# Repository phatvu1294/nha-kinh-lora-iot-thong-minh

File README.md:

# Nhà kính LoRa IOT thông minh 
*Nhà kính LoRa IOT thông minh được phát triển dựa trên ESP8266, Arduino, LoRa*  

### Giới thiệu
Hệ thống bao gồm 2 Node có nhiệm vụ thu thập dữ liệu sau đó gửi về Gateway thông qua công nghệ LoRa. Dữ liệu này sẽ được Gateway xử lý và đẩy lên Website thông qua giao thức MQTT. Giao diện Website được thiết kế với Blogger cho phép giám sát các thông số ở bất kỳ nơi đâu mà chúng ta có internet.

### Tính năng
- Với IOT chúng ta có thể theo dõi thiết bị ở mọi nơi miễn là có internet
- Với LoRa chúng ta có khoảng cách truyền lên đến hàng kilomet
- Giao diện Website trực quan, dễ nhìn, tên miền blogspot miễn phí
- Phím nhấn cho phép cài đặt WiFi của Gateway 1 cách dễ dàng
- Mạch một lớp giúp dễ dàng làm thủ công, thích hợp với sinh viên nghiên cứu khoa học

### Thông số kỹ thuật
#### Node
- Điện áp vào: 9-12VDC
- Màn hình hiển thị: LCD1602
- Socket cảm biến: DHT11/DHT22/LM35/CB Đất

#### Gateway
- Điện áp vào: 9-12VDC
- Socket hiển thị: LCD I2C

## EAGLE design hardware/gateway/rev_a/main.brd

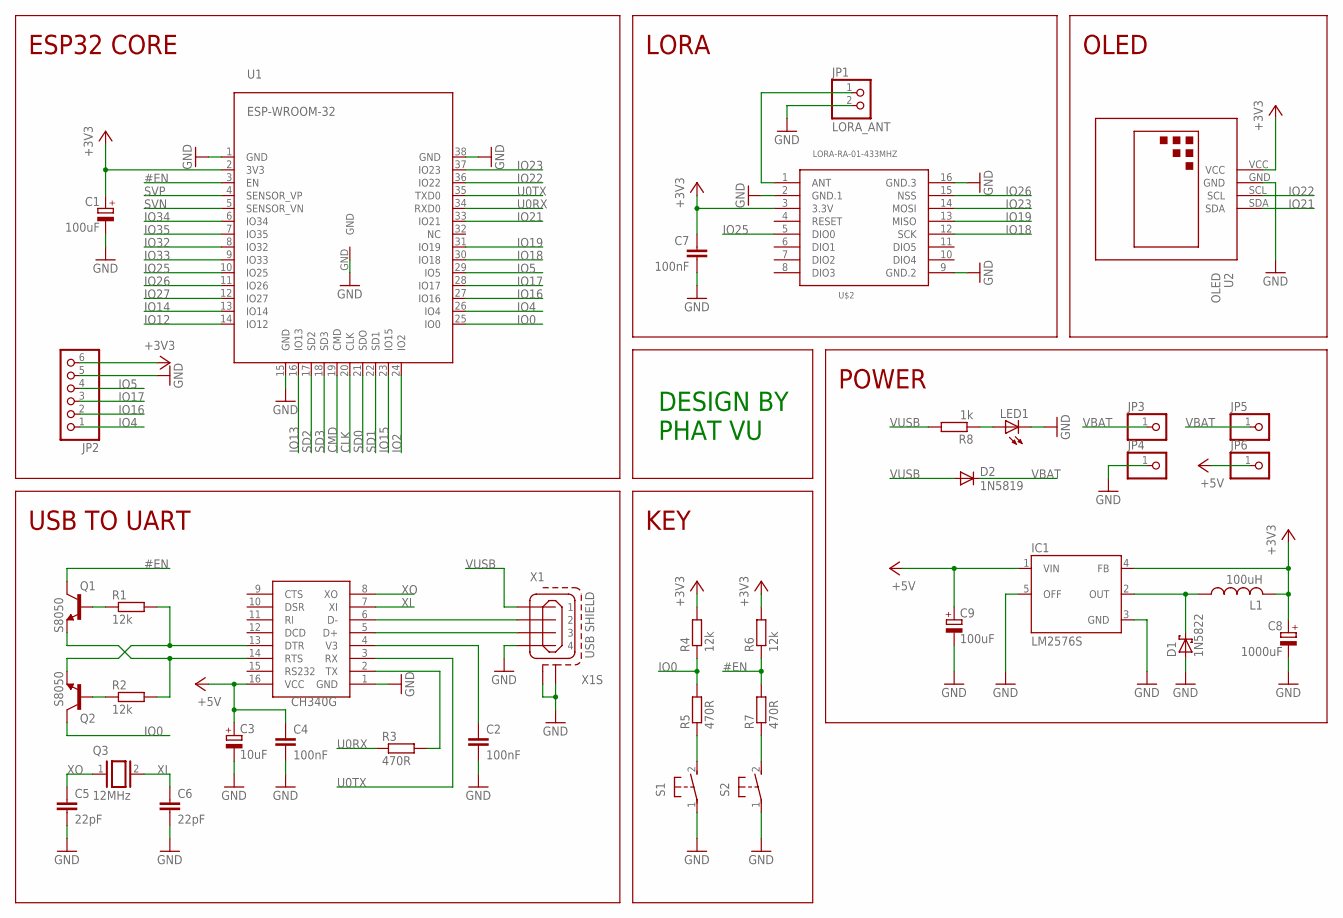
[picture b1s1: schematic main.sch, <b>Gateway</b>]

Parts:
C1, C9: 100uF; E5-10,5
C2, C4, C7: 100nF; C050-024X044
C3: 10uF; E2,5-6
C5, C6: 22pF; C050-024X044
C8: 1000uF; E5-13
D1: 1N5822; DO201T15
D2: 1N5819; DO41-10
IC1: LM2576S; TO263-5
JP1: LORA_ANT; 1X02
JP2: PINHD-1X6; 1X06
JP3, JP4, JP5, JP6: PINHD-1X1; 1X01
L1: 100uH; 6000-XXXX-RC
LED1: LED3MM
Q1, Q2: S8050; TO92-EBC
Q3: 12MHz; QS
R1, R2, R4, R6: 12k; 0207/10
R3, R5, R7: 470R; 0207/10
R8: 1k; 0207/10
S1, S2: 31-XX; B3F-31XX
U1: ESP-WROOM-32
U2: OLED; OLED-096-I2C
U$1: CH340G; SOIC16
U$2: LORA-RA-01-433MHZ; LORA-RA1-SMD
X1: USB SHIELD; 85-32004-00X

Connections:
#EN: Q1.C, R6.1, R7.2, U1.3 (EN)
+3V3: C1.+, C7.1, C8.+, IC1.4 (FB), JP2.6, L1.2, R4.2, R6.2, U1.2 (3V3), U2.VCC, U$2.3 (3.3V)
+5V: C3.+, C4.1, C9.+, IC1.1 (VIN), JP6.1, U$1.16 (VCC)
CLK: U1.20 (CLK)
CMD: U1.19 (CMD)
GND: C1.-, C2.2, C3.-, C4.2, C5.2, C6.2, C7.2, C8.-, C9.-, D1.A, IC1.3 (GND), IC1.5 (OFF), JP1.2, JP2.5, JP4.1, LED1.K (C), S1.1, S2.1, U1.1 (GND), U1.15 (GND), U1.38 (GND), U1.GND, U2.GND, U$1.1 (GND), U$2.2 (GND.1), U$2.9 (GND.2), U$2.16 (GND.3), X1.4, X1.M1 (S1), X1.M2 (S2)
IO0: Q2.C, R4.1, R5.2, U1.25 (IO0)
IO2: U1.24 (IO2)
IO4: JP2.1, U1.26 (IO4)
IO5: JP2.4, U1.29 (IO5)
IO12: U1.14 (IO12)
IO13: U1.16 (IO13)
IO14: U1.13 (IO14)
IO15: U1.23 (IO15)
IO16: JP2.2, U1.27 (IO16)
IO17: JP2.3, U1.28 (IO17)
IO18: U1.30 (IO18), U$2.12 (SCK)
IO19: U1.31 (IO19), U$2.13 (MISO)
IO21: U1.33 (IO21), U2.SDA
IO22: U1.36 (IO22), U2.SCL
IO23: U1.37 (IO23), U$2.14 (MOSI)
IO25: U1.10 (IO25), U$2.5 (DIO0)
IO26: U1.11 (IO26), U$2.15 (NSS)
IO27: U1.12 (IO27)
IO32: U1.8 (IO32)
IO33: U1.9 (IO33)
IO34: U1.6 (IO34)
IO35: U1.7 (IO35)
unnamed: JP1.1, U$2.1 (ANT)
unnamed: R3.2, U$1.2 (TX)
unnamed: U$1.6 (D-), X1.2
unnamed: U$1.5 (D+), X1.3
unnamed: C2.1, U$1.4 (V3)
unnamed: Q1.E, R2.2, U$1.14 (RTS)
unnamed: Q2.E, R1.2, U$1.13 (DTR)
unnamed: LED1.A, R8.1
unnamed: Q2.B, R2.1
unnamed: Q1.B, R1.1
unnamed: R7.1, S2.2 (S)
unnamed: R5.1, S1.2 (S)
unnamed: D1.C, IC1.2 (OUT), L1.1
SD0: U1.21 (SDO)
SD1: U1.22 (SD1)
SD2: U1.17 (SD2)
SD3: U1.18 (SD3)
SVN: U1.5 (SENSOR_VN)
SVP: U1.4 (SENSOR_VP)
U0RX: R3.1, U1.34 (RXD0)
U0TX: U1.35 (TXD0), U$1.3 (RX)
VBAT: D2.C, JP3.1, JP5.1
VUSB: D2.A, R8.2, X1.1
XI: C6.1, Q3.2, U$1.7 (XI)
XO: C5.1, Q3.1, U$1.8 (XO)

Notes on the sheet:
ESP32 CORE
USB TO UART
KEY
LORA
OLED
POWER
DESIGN BY PHAT VU

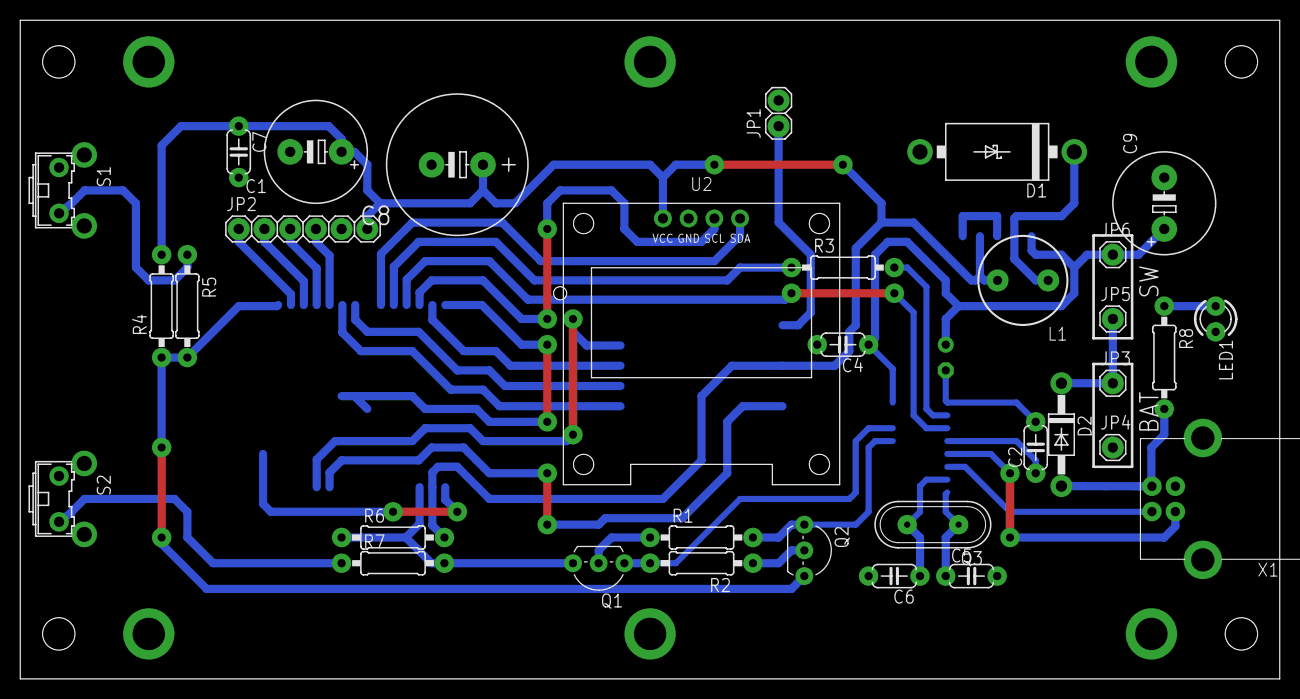
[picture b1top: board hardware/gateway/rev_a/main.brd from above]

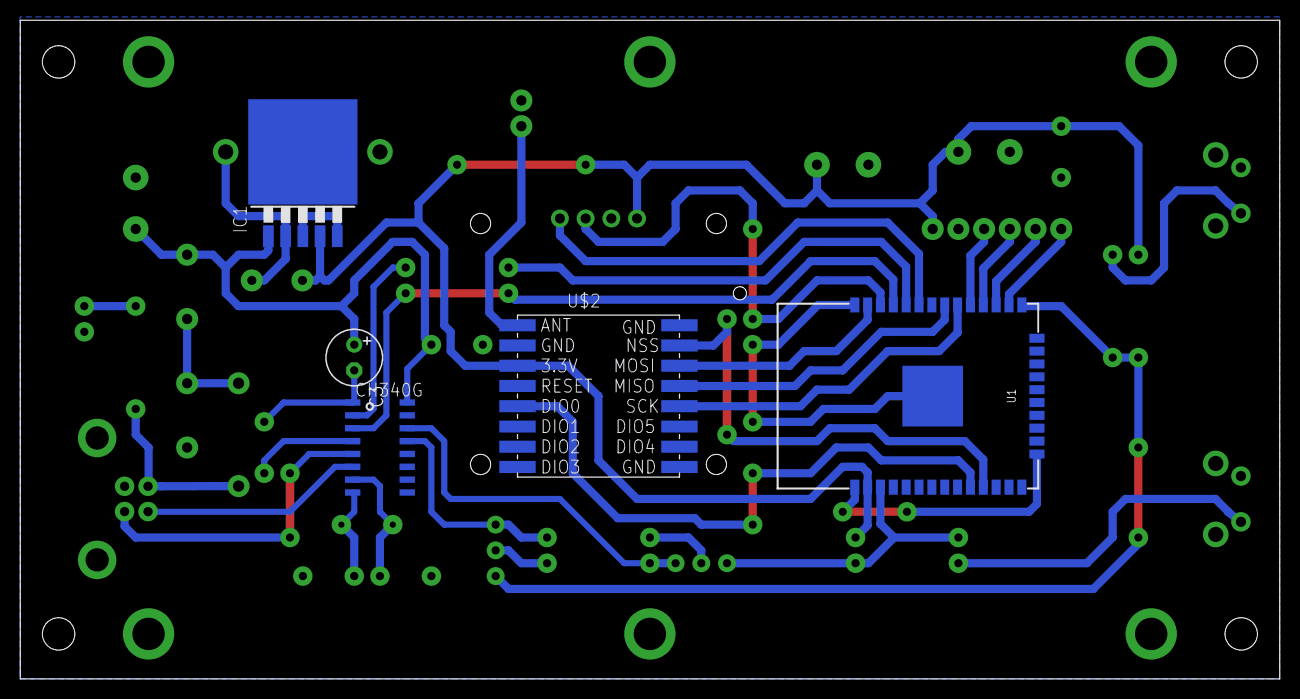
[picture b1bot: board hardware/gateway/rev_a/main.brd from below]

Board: 2 copper layers, 124.4 x 65.1 mm, 38 parts (5 on the bottom side), 35 nets.

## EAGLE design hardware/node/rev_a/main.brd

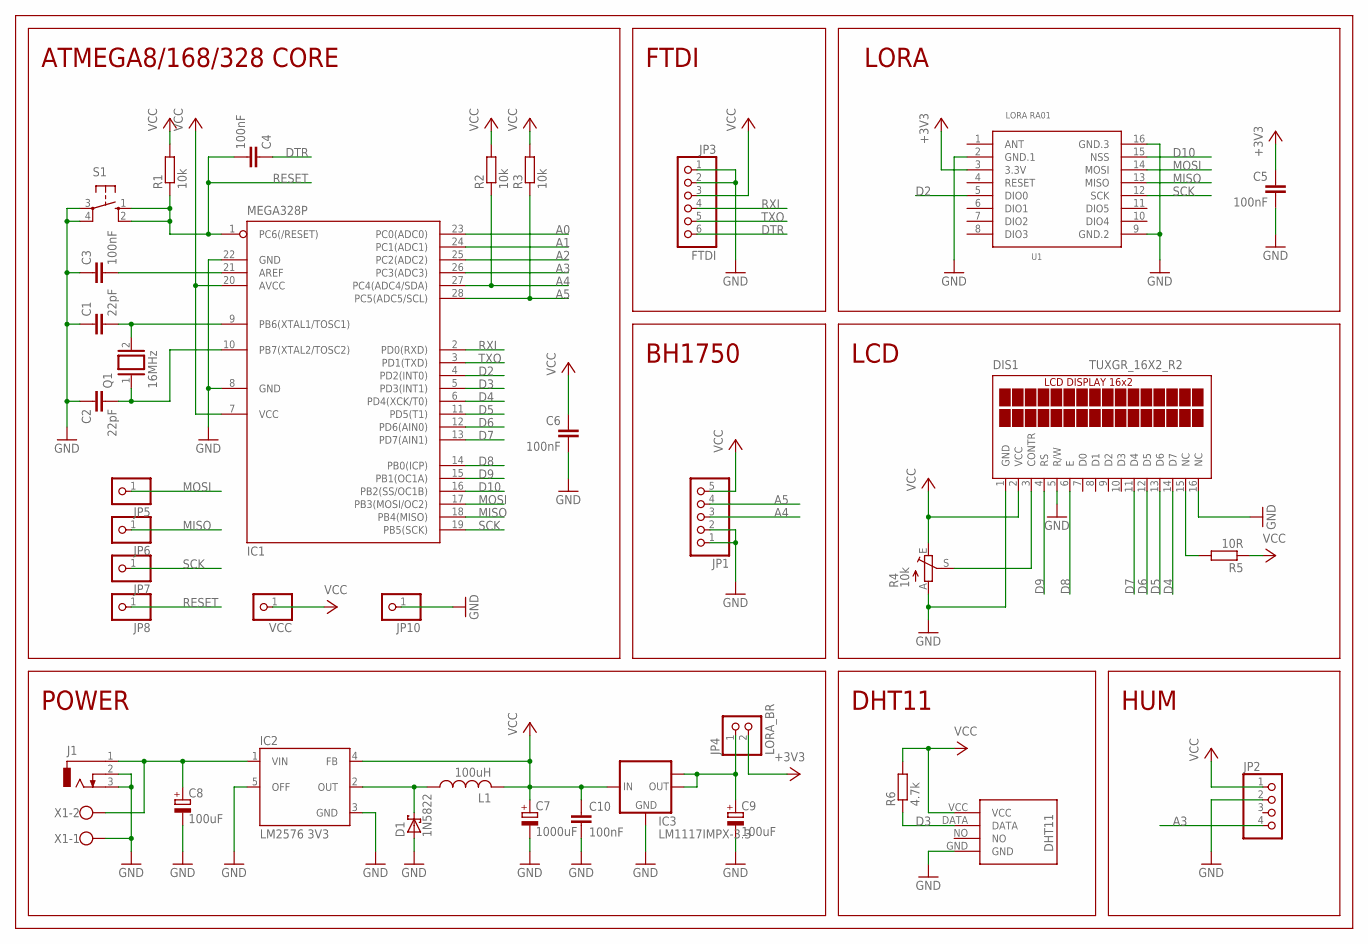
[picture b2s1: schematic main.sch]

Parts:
C1, C2: 22pF; C050-024X044
C3, C4, C5, C6, C10: 100nF; C050-024X044
C7: 1000uF; E5-13
C8: 100uF; E5-8,5
C9: 100uF; E3,5-10
D1: 1N5822; DO201T15
DIS1: TUXGR_16X2_R2
IC1: MEGA328P; DIL28-3
IC2: LM2576 3V3; TO263-5
IC3: LM1117IMPX-3.3; SOT223
J1: DCJ0303
JP1: PINHD-1X5; 1X05
JP2: PINHD-1X4; 1X04
JP3: FTDI; 1X06
JP4: LORA_BR; 1X02
JP5, JP6, JP7, JP8, JP10: PINHD-1X1; 1X01
L1: 100uH; 6000-XXXX-RC
Q1: 16MHz; QS
R1, R2, R3: 10k; 0207/10
R4: 10k; CA6V
R5: 10R; 0207/10
R6: 4.7k; 0207/10
S1: 10-XX; B3F-10XX
U1: LORA RA01; LORA-RA1-SMD
U$1: DHT11-PION.
VCC: PINHD-1X1; 1X01
X1: W237-102

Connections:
+3V3: C5.1, JP4.2, U1.3 (3.3V)
A0: IC1.23 (PC0(ADC0))
A1: IC1.24 (PC1(ADC1))
A2: IC1.25 (PC2(ADC2))
A3: IC1.26 (PC3(ADC3)), JP2.4
A4: IC1.27 (PC4(ADC4/SDA)), JP1.3, R2.1
A5: IC1.28 (PC5(ADC5/SCL)), JP1.4, R3.1
D2: IC1.4 (PD2(INT0)), U1.5 (DIO0)
D3: IC1.5 (PD3(INT1)), R6.1, U$1.DATA
D4: DIS1.14 (D7), IC1.6 (PD4(XCK/T0))
D5: DIS1.13 (D6), IC1.11 (PD5(T1))
D6: DIS1.12 (D5), IC1.12 (PD6(AIN0))
D7: DIS1.11 (D4), IC1.13 (PD7(AIN1))
D8: DIS1.6 (E), IC1.14 (PB0(ICP))
D9: DIS1.4 (RS), IC1.15 (PB1(OC1A))
D10: IC1.16 (PB2(SS/OC1B)), U1.15 (NSS)
DTR: C4.1, JP3.6
GND: C1.1, C2.1, C3.1, C5.2, C6.2, C7.-, C8.-, C9.-, C10.2, D1.A, DIS1.1 (GND), DIS1.5 (R/W), DIS1.16 (NC), IC1.8 (GND), IC1.22 (GND), IC2.3 (GND), IC2.5 (OFF), IC3.1 (GND), J1.2, J1.3, JP1.1, JP1.2, JP2.2, JP3.1, JP3.2, JP10.1, R4.A, S1.3, S1.4 (P1), U1.2 (GND.1), U1.9 (GND.2), U1.16 (GND.3), U$1.GND, X1.1
MISO: IC1.18 (PB4(MISO)), JP6.1, U1.13 (MISO)
MOSI: IC1.17 (PB3(MOSI/OC2)), JP5.1, U1.14 (MOSI)
unnamed: C1.2, IC1.9 (PB6(XTAL1/TOSC1)), Q1.2
unnamed: C2.2, IC1.10 (PB7(XTAL2/TOSC2)), Q1.1
unnamed: C3.2, IC1.21 (AREF)
unnamed: C8.+, IC2.1 (VIN), J1.1, X1.2
unnamed: D1.C, IC2.2 (OUT), L1.1
unnamed: C9.+, IC3.2 (OUT), IC3.TAB (OUT1), JP4.1
unnamed: DIS1.15 (NC), R5.2
unnamed: DIS1.3 (CONTR), R4.S
RESET: C4.2, IC1.1 (PC6(/RESET)), JP8.1, R1.1, S1.1 (S), S1.2 (S1)
RXI: IC1.2 (PD0(RXD)), JP3.4
SCK: IC1.19 (PB5(SCK)), JP7.1, U1.12 (SCK)
TXO: IC1.3 (PD1(TXD)), JP3.5
VCC: C6.1, C7.+, C10.1, DIS1.2 (VCC), IC1.7 (VCC), IC1.20 (AVCC), IC2.4 (FB), IC3.3 (IN), JP1.5, JP2.1, JP3.3, L1.2, R1.2, R2.2, R3.2, R4.E, R5.1, R6.2, U$1.VCC, VCC.1

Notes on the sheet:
LORA
ATMEGA8/168/328 CORE
FTDI
POWER
BH1750
LCD
DHT11
HUM

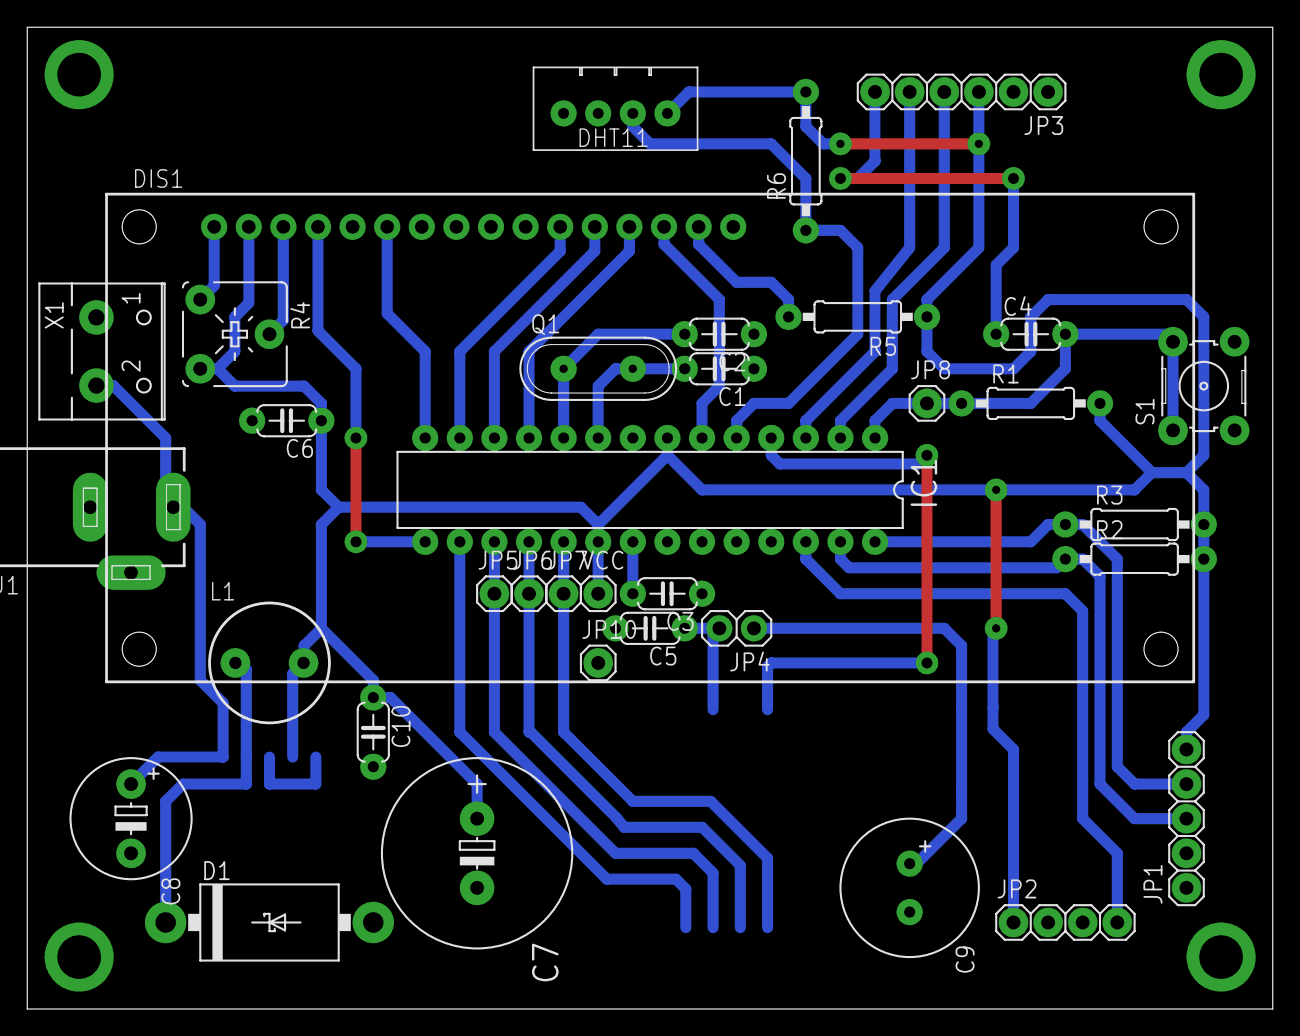
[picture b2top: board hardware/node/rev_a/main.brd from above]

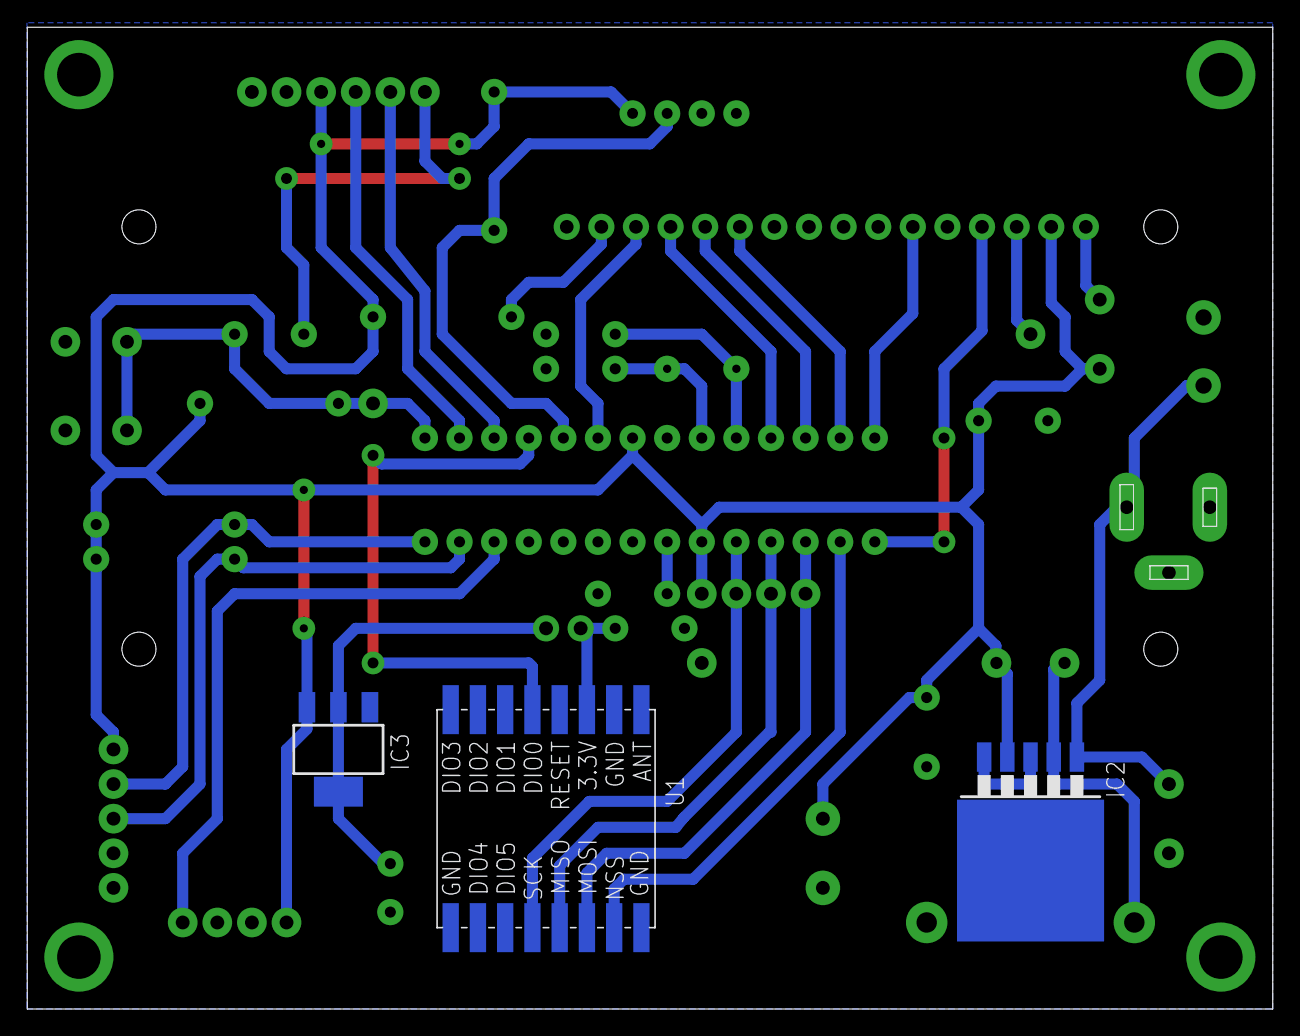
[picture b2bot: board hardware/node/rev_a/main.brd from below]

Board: 2 copper layers, 91.4 x 72.1 mm, 38 parts (3 on the bottom side), 30 nets.

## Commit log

2020-02-15 source
2020-02-15 thêm source
2020-02-16 them pcb
2020-02-17 them pcb gateway
2020-02-17 sua pcb
2020-02-17 sửa mã nguồn
2020-02-17 sửa readme.md
2020-02-17 thêm ảnh readme
2020-02-21 sửa mã nguôn
2020-02-29 cập nhật thêm điều khiển bằng IR
2021-04-01 update image
